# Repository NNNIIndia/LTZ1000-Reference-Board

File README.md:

# LTZ1000-Reference-Board
## Bare-bones LTZ1000 carrier PCB
In my experience, I've found that some things work best when you just leave them alone. I guess the same thing applies for precision voltage references - the less you bother them, the better. Just let them do their thing. This board was designed in that spirit - no weird thermal cutouts, no bizzaire crop circles (okay, maybe just one).

The overall form factor and layout of this board was inspired by the reference board from the HP3458A 8.5 digit multimeter, while the (3D-printed) plastic cap comes from both the 3458A and Keithely 2002 8.5 digit multimeter. If it was good enough for them, it's good enough for me.

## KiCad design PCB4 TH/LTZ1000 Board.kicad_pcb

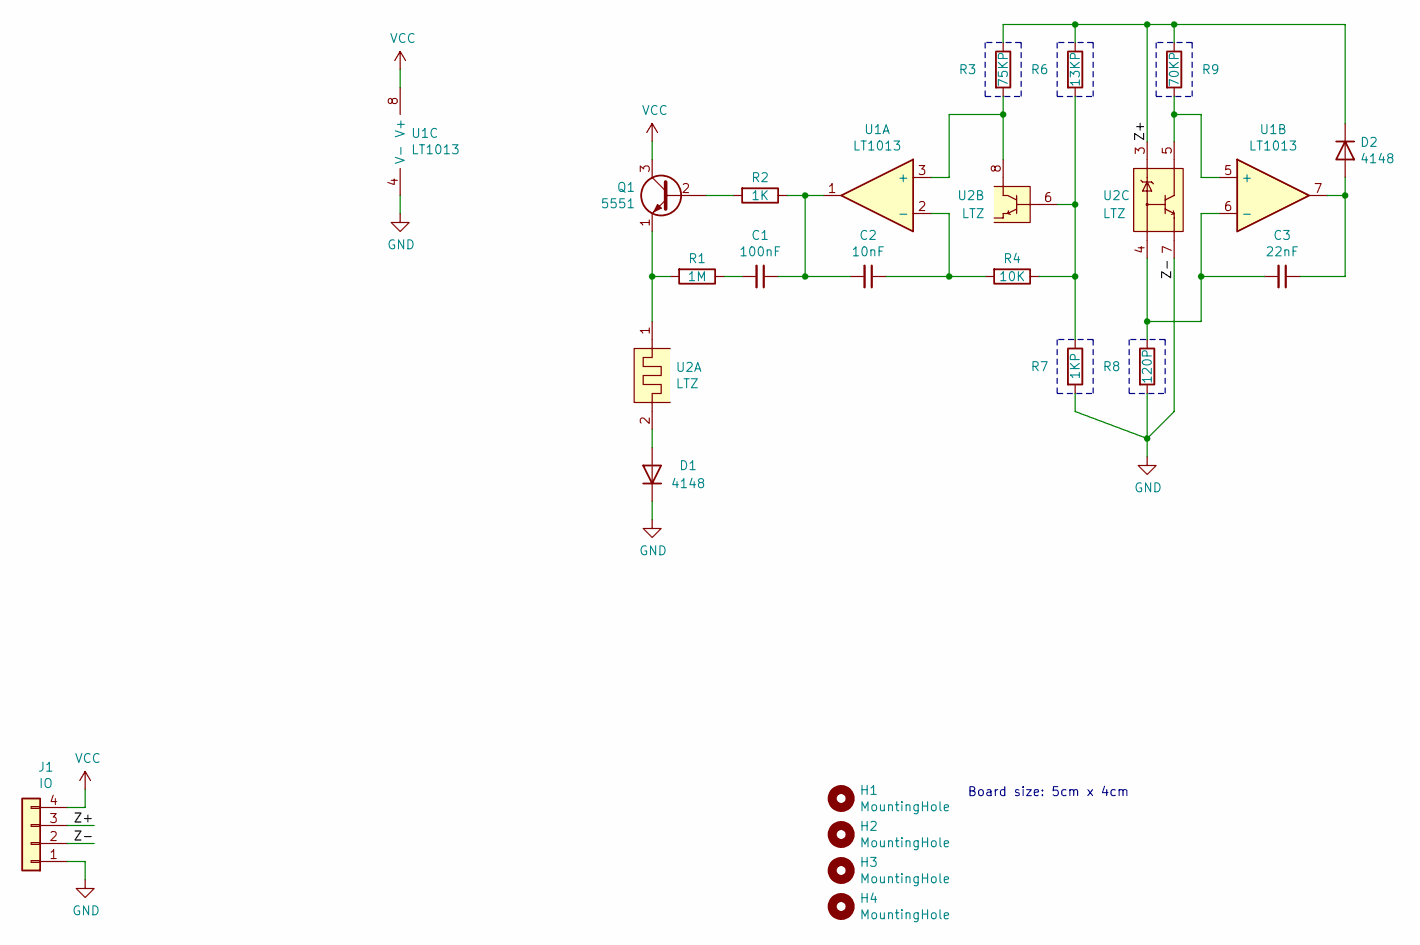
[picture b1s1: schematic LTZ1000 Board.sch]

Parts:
C1: 100nF; C_Rect_L7.0mm_W2.0mm_P5.00mm
C2: 10nF; C_Rect_L7.0mm_W2.0mm_P5.00mm
C3: 22nF; C_Rect_L7.0mm_W2.0mm_P5.00mm
D1, D2: 4148; D_DO-35_SOD27_P7.62mm_Horizontal
H1, H2, H3, H4: MountingHole; MountingHole_3mm_Pad_Via
J1: IO; PinHeader_1x04_P2.54mm_Vertical
Q1: 5551; TO-92
R1: 1M; R_Axial_DIN0207_L6.3mm_D2.5mm_P10.16mm_Horizontal
R2: 1K; R_Axial_DIN0207_L6.3mm_D2.5mm_P10.16mm_Horizontal
R3: 75KP; R_Box_L8.4mm_W2.5mm_P5.08mm
R4: 10K; R_Axial_DIN0207_L6.3mm_D2.5mm_P10.16mm_Horizontal
R6: 13KP; R_Box_L8.4mm_W2.5mm_P5.08mm
R7: 1KP; R_Box_L8.4mm_W2.5mm_P5.08mm
R8: 120P; R_Box_L8.4mm_W2.5mm_P5.08mm
R9: 70KP; R_Box_L8.4mm_W2.5mm_P5.08mm
U1: LT1013; DIP-8_W7.62mm
U2: LTZ; TO-99-8

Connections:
/Z+: D2.1 (K), J1.3, R3.1, R6.1, R9.1, U2.3 (Z+)
GND: D1.1 (K), J1.1, J1.2, R7.2, R8.2, U1.4 (V-), U2.7 (COM)
unnamed: C1.1, C2.2, R2.1, U1.1
unnamed: C1.2, R1.1
unnamed: C2.1, R4.2, U1.2 (-)
unnamed: C3.1, D2.2 (A), U1.7
unnamed: C3.2, R8.1, U1.6 (-), U2.4 (Z-)
unnamed: D1.2 (A), U2.2 (HEATER)
unnamed: Q1.1 (E), R1.2, U2.1 (HEATER)
unnamed: Q1.2 (B), R2.2
unnamed: R3.2, U1.3 (+), U2.8 (TC)
unnamed: R4.1, R6.2, R7.1, U2.6 (TS)
unnamed: R9.2, U1.5 (+), U2.5 (C)
VCC: J1.4, Q1.3 (C), U1.8 (V+)

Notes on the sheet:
Board size: 5cm x 4cm

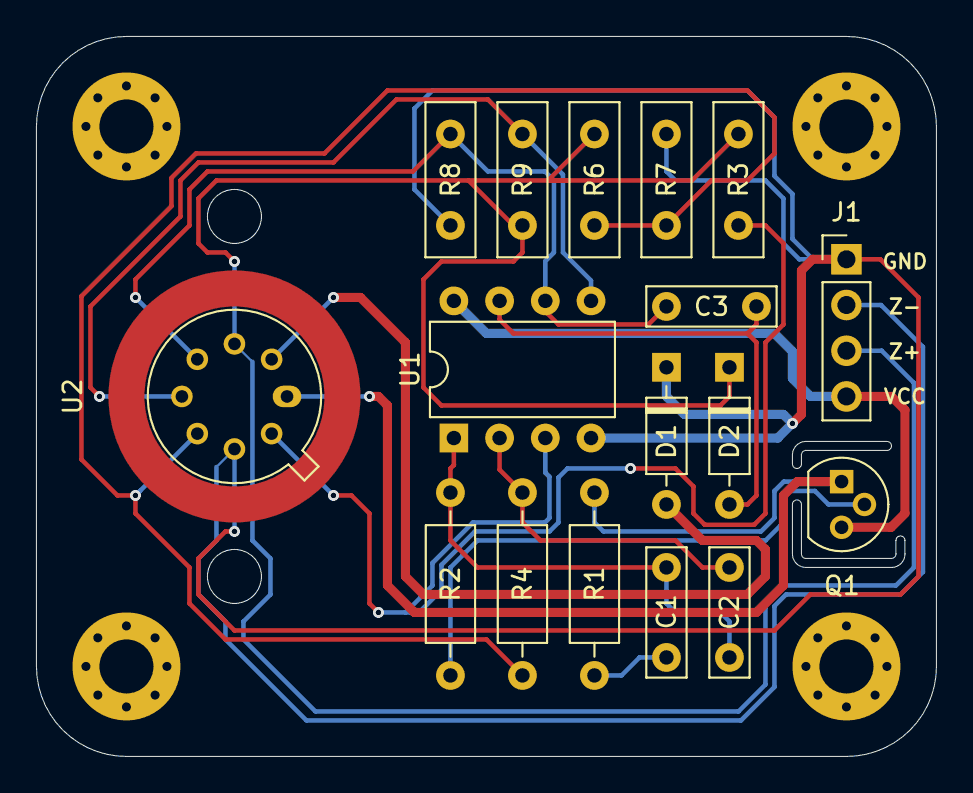
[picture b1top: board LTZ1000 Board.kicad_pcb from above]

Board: 2 copper layers, 50.0 x 40.0 mm, 21 parts (0 on the bottom side), 14 nets.

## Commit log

2021-12-30 Pictures and 3D printing files added
